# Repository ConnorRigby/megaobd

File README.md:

# MegaOBD
obd2 simulator addon for MS3 based ECUs. Currently targeted at the 01-05 
Mazda Miata.  

## Building the code
either use the Arduino IDE, or just call `make`

## Relevant docs
[Miata ECU hacking](http://ecuhacking101.blogspot.com/2011/01/nb-miata-obd-mode-2.html)
[OBD2 pids](https://en.wikipedia.org/wiki/OBD-II_PIDs#Modes)

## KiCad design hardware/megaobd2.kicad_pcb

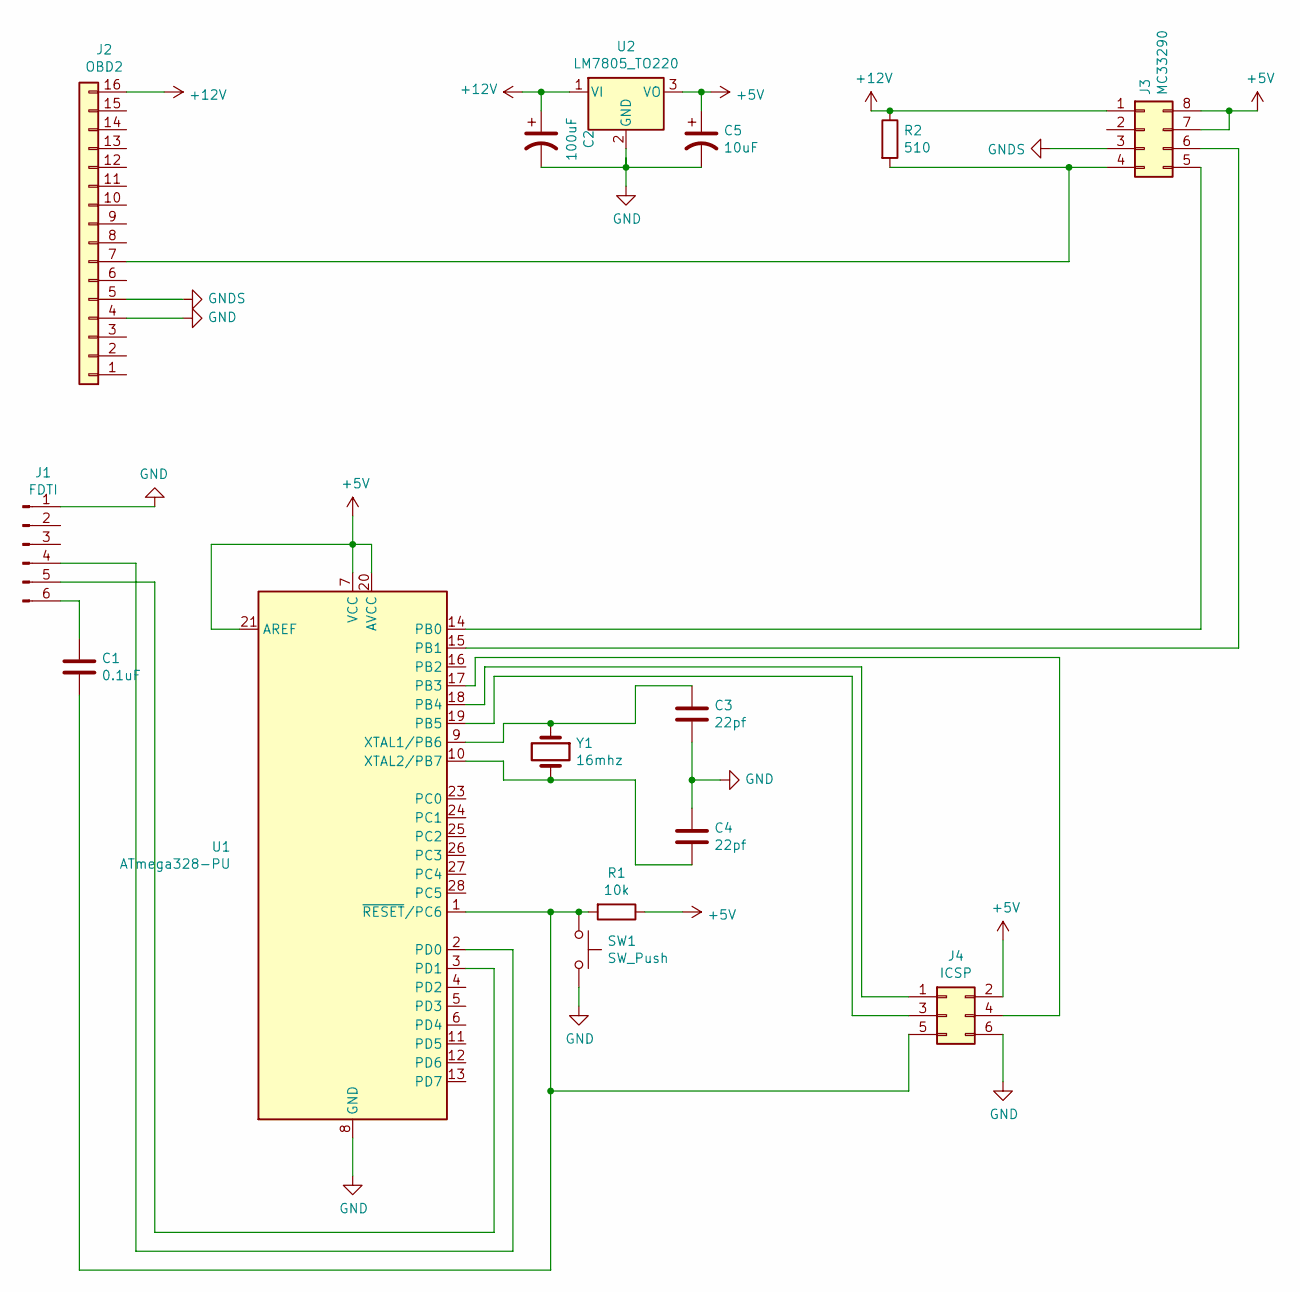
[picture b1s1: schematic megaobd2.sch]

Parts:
C1: 0.1uF; C_Disc_D5.1mm_W3.2mm_P5.00mm
C2: 100uF; CP_Radial_D5.0mm_P2.50mm
C3, C4: 22pf; C_Disc_D3.8mm_W2.6mm_P2.50mm
C5: 10uF; CP_Radial_D5.0mm_P2.50mm
J1: FDTI; PinSocket_1x06_P2.54mm_Vertical
J2: OBD2; PinSocket_2x08_P2.54mm_Vertical
J3: MC33290; SOIC-8_3.9x4.9mm_P1.27mm
J4: ICSP; PinHeader_2x03_P2.54mm_Vertical
R1: 10k; R_Axial_DIN0207_L6.3mm_D2.5mm_P7.62mm_Horizontal
R2: 510; R_Axial_DIN0207_L6.3mm_D2.5mm_P7.62mm_Horizontal
SW1: SW_Push; SW_CW_GPTS203211B
U1: ATmega328-PU; DIP-28_W7.62mm
U2: LM7805_TO220; TO-220-3_Vertical
Y1: 16mhz; Crystal_HC49-U_Vertical

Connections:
+5V: C5.1, J3.7, J3.8, J4.2, R1.1, U1.7 (VCC), U1.20 (AVCC), U1.21 (AREF), U2.3 (VO)
+12V: C2.1, J2.16, J3.1, R2.1, U2.1 (VI)
GND: C2.2, C3.2, C4.1, C5.2, J1.1, J2.4, J4.6, SW1.2, U1.8 (GND), U1.22 (GND), U2.2 (GND)
GNDS: J2.5, J3.3
unnamed: C1.1, J1.6
unnamed: C1.2, J4.5, R1.2, SW1.1, U1.1 (~RESET~/PC6)
unnamed: C3.1, U1.9 (XTAL1/PB6), Y1.1
unnamed: C4.2, U1.10 (XTAL2/PB7), Y1.2
unnamed: J1.4, U1.2 (PD0)
unnamed: J1.5, U1.3 (PD1)
unnamed: J2.7, J3.4, R2.2
unnamed: J3.5, U1.14 (PB0)
unnamed: J3.6, U1.15 (PB1)
unnamed: J4.1, U1.18 (PB4)
unnamed: J4.3, U1.19 (PB5)
unnamed: J4.4, U1.17 (PB3)

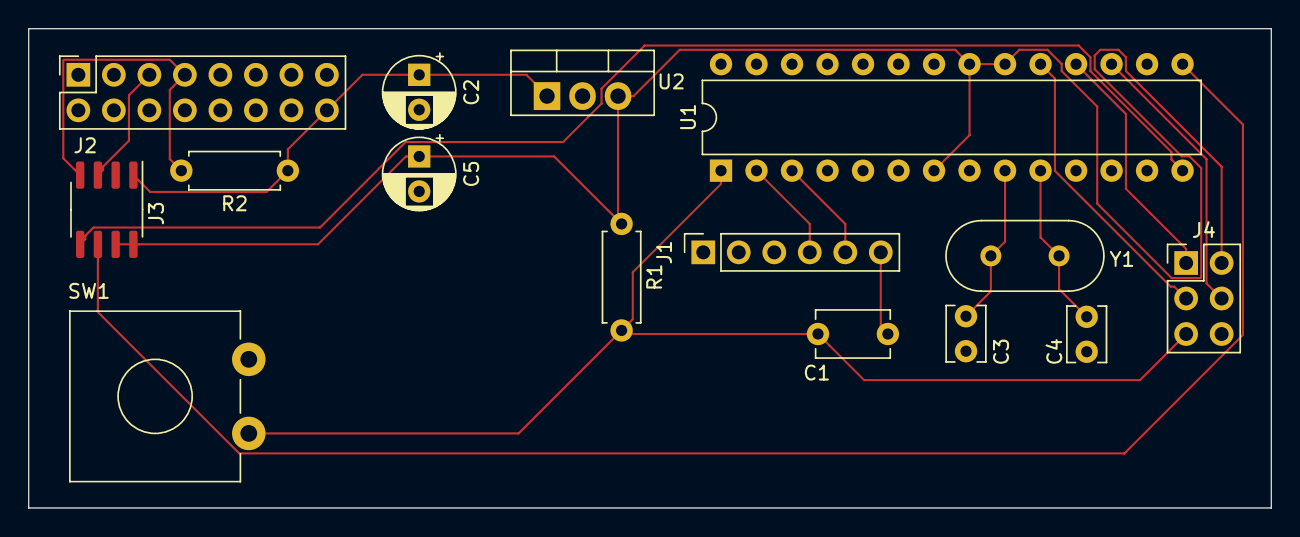
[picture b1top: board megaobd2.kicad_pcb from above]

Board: 2 copper layers, 88.9 x 34.3 mm, 15 parts (0 on the bottom side), 16 nets.

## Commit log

2019-08-14 Initial Makefile for Arduino projects
2019-08-14 Use superior arduino build system to maintain sanity
2019-08-14 Add PCB design files
2019-08-15 Initial pass at reading megasquirt data. Untested
2019-08-15 Implement OBD mode 1
2019-08-15 Add helpful docs to README
2019-08-16 Begin implementing Mode 2
